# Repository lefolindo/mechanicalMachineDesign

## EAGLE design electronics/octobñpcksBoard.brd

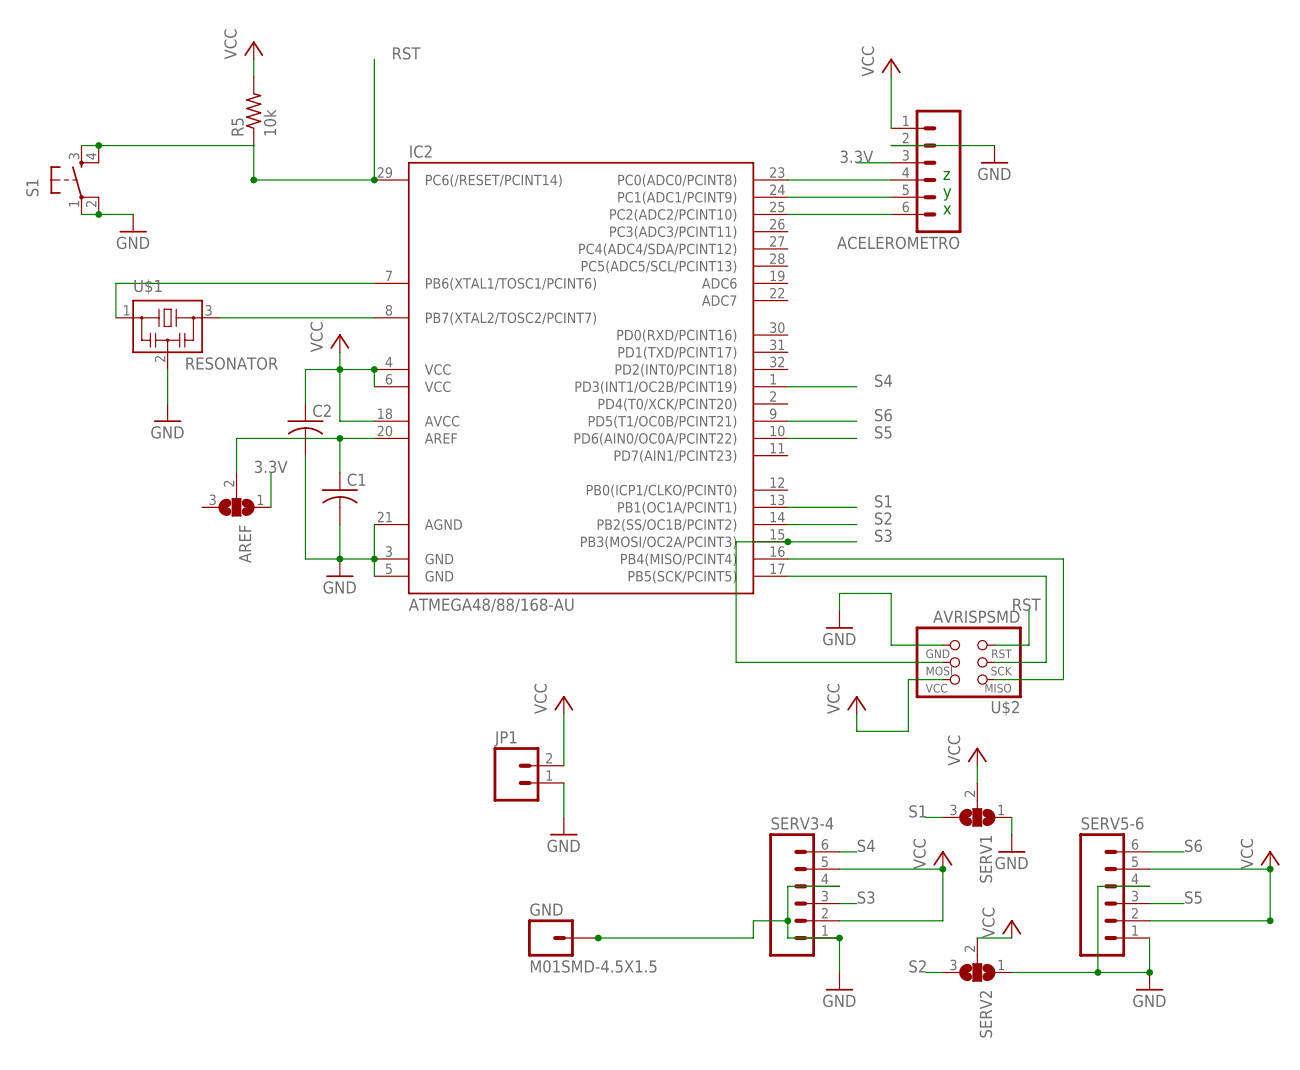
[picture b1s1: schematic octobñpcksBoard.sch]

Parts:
ACELEROMETRO: M06SMD; 1X06-SMD
AREF: SJ2WW; SJ_2W
C1, C2: C-USC1206; C1206
GND: M01SMD-4.5X1.5; PAD-1.5X4.5
IC2: ATMEGA48/88/168-AU; TQFP32-08
JP1: M02; 1X02_LONGPADS
R5: 10k; 1206
S1: 6MM_SWITCH6MM_SWITCH; 6MM_SWITCH
SERV1, SERV2: SJ2WW; SJ_2W
SERV3-4, SERV5-6: M06SMD; 1X06-SMD
U$1: RESONATOR; EFOBM
U$2: AVRISPSMD; 2X03SMD

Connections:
3.3V: ACELEROMETRO.3, AREF.1
GND: ACELEROMETRO.2, C1.2, C2.2, GND.P$1, IC2.3 (GND), IC2.5 (GND), IC2.21 (AGND), JP1.1, S1.1, S1.2 (P1), SERV1.1, SERV2.1, SERV3-4.1, SERV3-4.4, SERV5-6.1, SERV5-6.4, U$1.2, U$2.6 (GND)
unnamed: IC2.17 (PB5(SCK/PCINT5)), U$2.3 (SCK)
unnamed: ACELEROMETRO.4, IC2.23 (PC0(ADC0/PCINT8))
unnamed: IC2.16 (PB4(MISO/PCINT4)), U$2.1 (MISO)
unnamed: IC2.8 (PB7(XTAL2/TOSC2/PCINT7)), U$1.3
unnamed: IC2.7 (PB6(XTAL1/TOSC1/PCINT6)), U$1.1
unnamed: AREF.2, C1.1, IC2.20 (AREF)
unnamed: ACELEROMETRO.5, IC2.24 (PC1(ADC1/PCINT9))
unnamed: ACELEROMETRO.6, IC2.25 (PC2(ADC2/PCINT10))
RST: IC2.29 (PC6(/RESET/PCINT14)), R5.1, S1.3 (S), S1.4 (S1), U$2.5 (RST)
S1: IC2.13 (PB1(OC1A/PCINT1)), SERV1.3
S2: IC2.14 (PB2(SS/OC1B/PCINT2)), SERV2.3
S3: IC2.15 (PB3(MOSI/OC2A/PCINT3)), SERV3-4.3, U$2.4 (MOSI)
S4: IC2.1 (PD3(INT1/OC2B/PCINT19)), SERV3-4.6
S5: IC2.10 (PD6(AIN0/OC0A/PCINT22)), SERV5-6.3
S6: IC2.9 (PD5(T1/OC0B/PCINT21)), SERV5-6.6
VCC: ACELEROMETRO.1, C2.1, IC2.4 (VCC), IC2.6 (VCC), IC2.18 (AVCC), JP1.2, R5.2, SERV1.2, SERV2.2, SERV3-4.2, SERV3-4.5, SERV5-6.2, SERV5-6.5, U$2.2 (VCC)

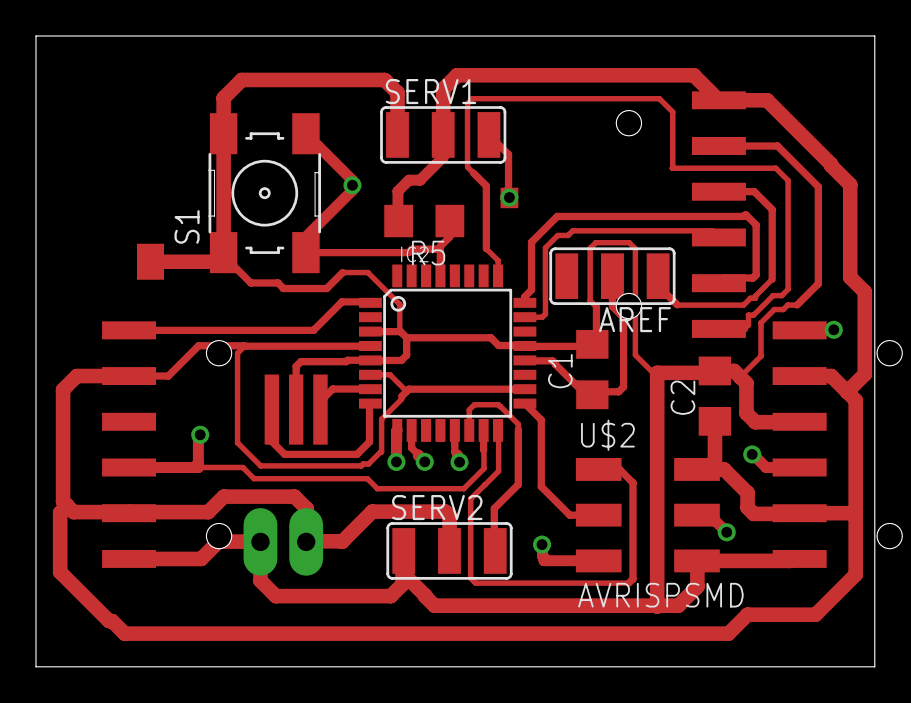
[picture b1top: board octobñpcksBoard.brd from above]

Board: 2 copper layers, 46.6 x 35.0 mm, 15 parts (0 on the bottom side), 18 nets.

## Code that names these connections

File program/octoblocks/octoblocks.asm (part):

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	;----------------------------------------------------
	;------POSICIONES SERVO1 Y SERVO2-TIMER1-------------

		   ;DUTYC. EN OCR1A-PB1 SERVO1  
	   LDI R16,HIGH(1360)
       STS OCR1AH,R16
       LDI R16,LOW(1360)   
       STS OCR1AL,R16
	
		;;DUTYC. EN OCR1B-PB1 SERVO2 
	   LDI R16,HIGH(1480)
       STS OCR1BH,R16
       LDI R16,LOW(1480)   
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	;---------------------------------------------------
	;------POSICIONES SERVO3 Y SERVO4-TIMER2------------

		;DUTYC. EN PB3-SERVO3 0 grados, 

		LDI R16,21
       	STS OCR2A,R16

		;DUTYC. EN PD3-SERVO4 0 grados, 
	
	   	LDI R16,21
       	STS OCR2B,R16
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	;---------------------------------------------------------
	;------POSICIONES SERVO5 Y SERVO6-TIMER0---------------

		;DUTYC. EN PD6-SERVO5, 0 grados, 

		LDI R16,23
       	OUT OCR0A,R16

		;DUTYC. EN PD5-SERVO6, 0 grados, 
	
	   	LDI R16,23
       	OUT OCR0B,R16
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
	

		; DUTYC. EN OCR1A-PB1 SERVO1  
	   LDI R16,HIGH(1764)
       STS OCR1AH,R16
       LDI R16,LOW(1764)   
       STS OCR1AL,R16

	   	;DUTYC. EN OCR1B-PB1 SERVO2 
	   LDI R16,HIGH(1894)
       STS OCR1BH,R16
       LDI R16,LOW(1894)   
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	;---------------------------------------------------
	;------POSICIONES SERVO3 Y SERVO4-TIMER2------------

		;DUTYC. EN PB3-SERVO3 -45 grados, 

		LDI R16,14
       	STS OCR2A,R16

		;DUTYC. EN PD3-SERVO4 +45 grados, 
	
	   	LDI R16,14
       	STS OCR2B,R16
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	;---------------------------------------------------------
	;------POSICIONES SERVO5 Y SERVO6-TIMER0---------------

		;DUTYC. EN PD6-SERVO5, 0 grados, 

		LDI R16,23
       	OUT OCR0A,R16

		;DUTYC. EN PD5-SERVO6, 0 grados, 
	
	   	LDI R16,23
       	OUT OCR0B,R16
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	;---------------------------------------------------------
	;---------POSICIONES SERVO1 Y SERVO2-TIMER1---------------

	 ;DUTYC. EN OCR1A-PB1 SERVO1  
	   LDI R16,HIGH(1360)
       STS OCR1AH,R16
       LDI R16,LOW(1360)   
       STS OCR1AL,R16
	
		;;DUTYC. EN OCR1B-PB1 SERVO2 
	   LDI R16,HIGH(1480)
       STS OCR1BH,R16
       LDI R16,LOW(1480)   
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	;---------------------------------------------------------
	;---------POSICIONES SERVO3 Y SERVO4-TIMER2---------------

	;DUTYC. EN PB3-SERVO3 -45 grados, 

		LDI R16,14
       	STS OCR2A,R16

		;DUTYC. EN PD3-SERVO4 +45 grados, 
	
	   	LDI R16,14
       	STS OCR2B,R16
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       LDI R16,LOW(890)    
       STS OCR1AL,R16

	;DUTYC. OCR1B - PB1-SERVO2 
	   LDI R16,HIGH(1065)
       STS OCR1BH,R16
       LDI R16,LOW(1065)   
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	;---------POSICIONES SERVO3 Y SERVO4-TIMER2---------------


	;DUTYC. EN PB3-SERVO3 0 grados, 

		LDI R16,21
       	STS OCR2A,R16

		;DUTYC. EN PD3-SERVO4 0 grados, 
	
	   	LDI R16,21
       	STS OCR2B,R16
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	;---------POSICIONES SERVO1 Y SERVO2-TIMER1---------------

	
	 ;DUTYC. EN OCR1A-PB1 SERVO1  
	   LDI R16,HIGH(1360)
       STS OCR1AH,R16
       LDI R16,LOW(1360)   
       STS OCR1AL,R16
	
		;;DUTYC. EN OCR1B-PB1 SERVO2 
	   LDI R16,HIGH(1480)
       STS OCR1BH,R16
       LDI R16,LOW(1480)   
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	;---------------------------------------------------
	;------POSICIONES SERVO3 Y SERVO4-TIMER2------------

		;DUTYC. EN PB3-SERVO3 0 grados, 

		LDI R16,21
       	STS OCR2A,R16

		;DUTYC. EN PD3-SERVO4 0 grados, 
	
	   	LDI R16,21
       	STS OCR2B,R16
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	;---------------------------------------------------------
	;------POSICIONES SERVO5 Y SERVO6-TIMER0---------------

		;DUTYC. EN PD6-SERVO5, 0 grados, 

		LDI R16,23
       	OUT OCR0A,R16

		;DUTYC. EN PD5-SERVO6, 0 grados, 
	
	   	LDI R16,23
       	OUT OCR0B,R16
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
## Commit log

2014-06-23 mechanocal design

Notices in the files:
parts and their libraries:
01_SparkFun: Licensing: CC v3.0 Share-Alike You are welcome to use this library for commercial purposes.
